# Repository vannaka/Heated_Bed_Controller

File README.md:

Heated_Bed_Controller

# PCB Images

# Prototyping

# Screen & Nob

# Wiring

# Bed & Printer

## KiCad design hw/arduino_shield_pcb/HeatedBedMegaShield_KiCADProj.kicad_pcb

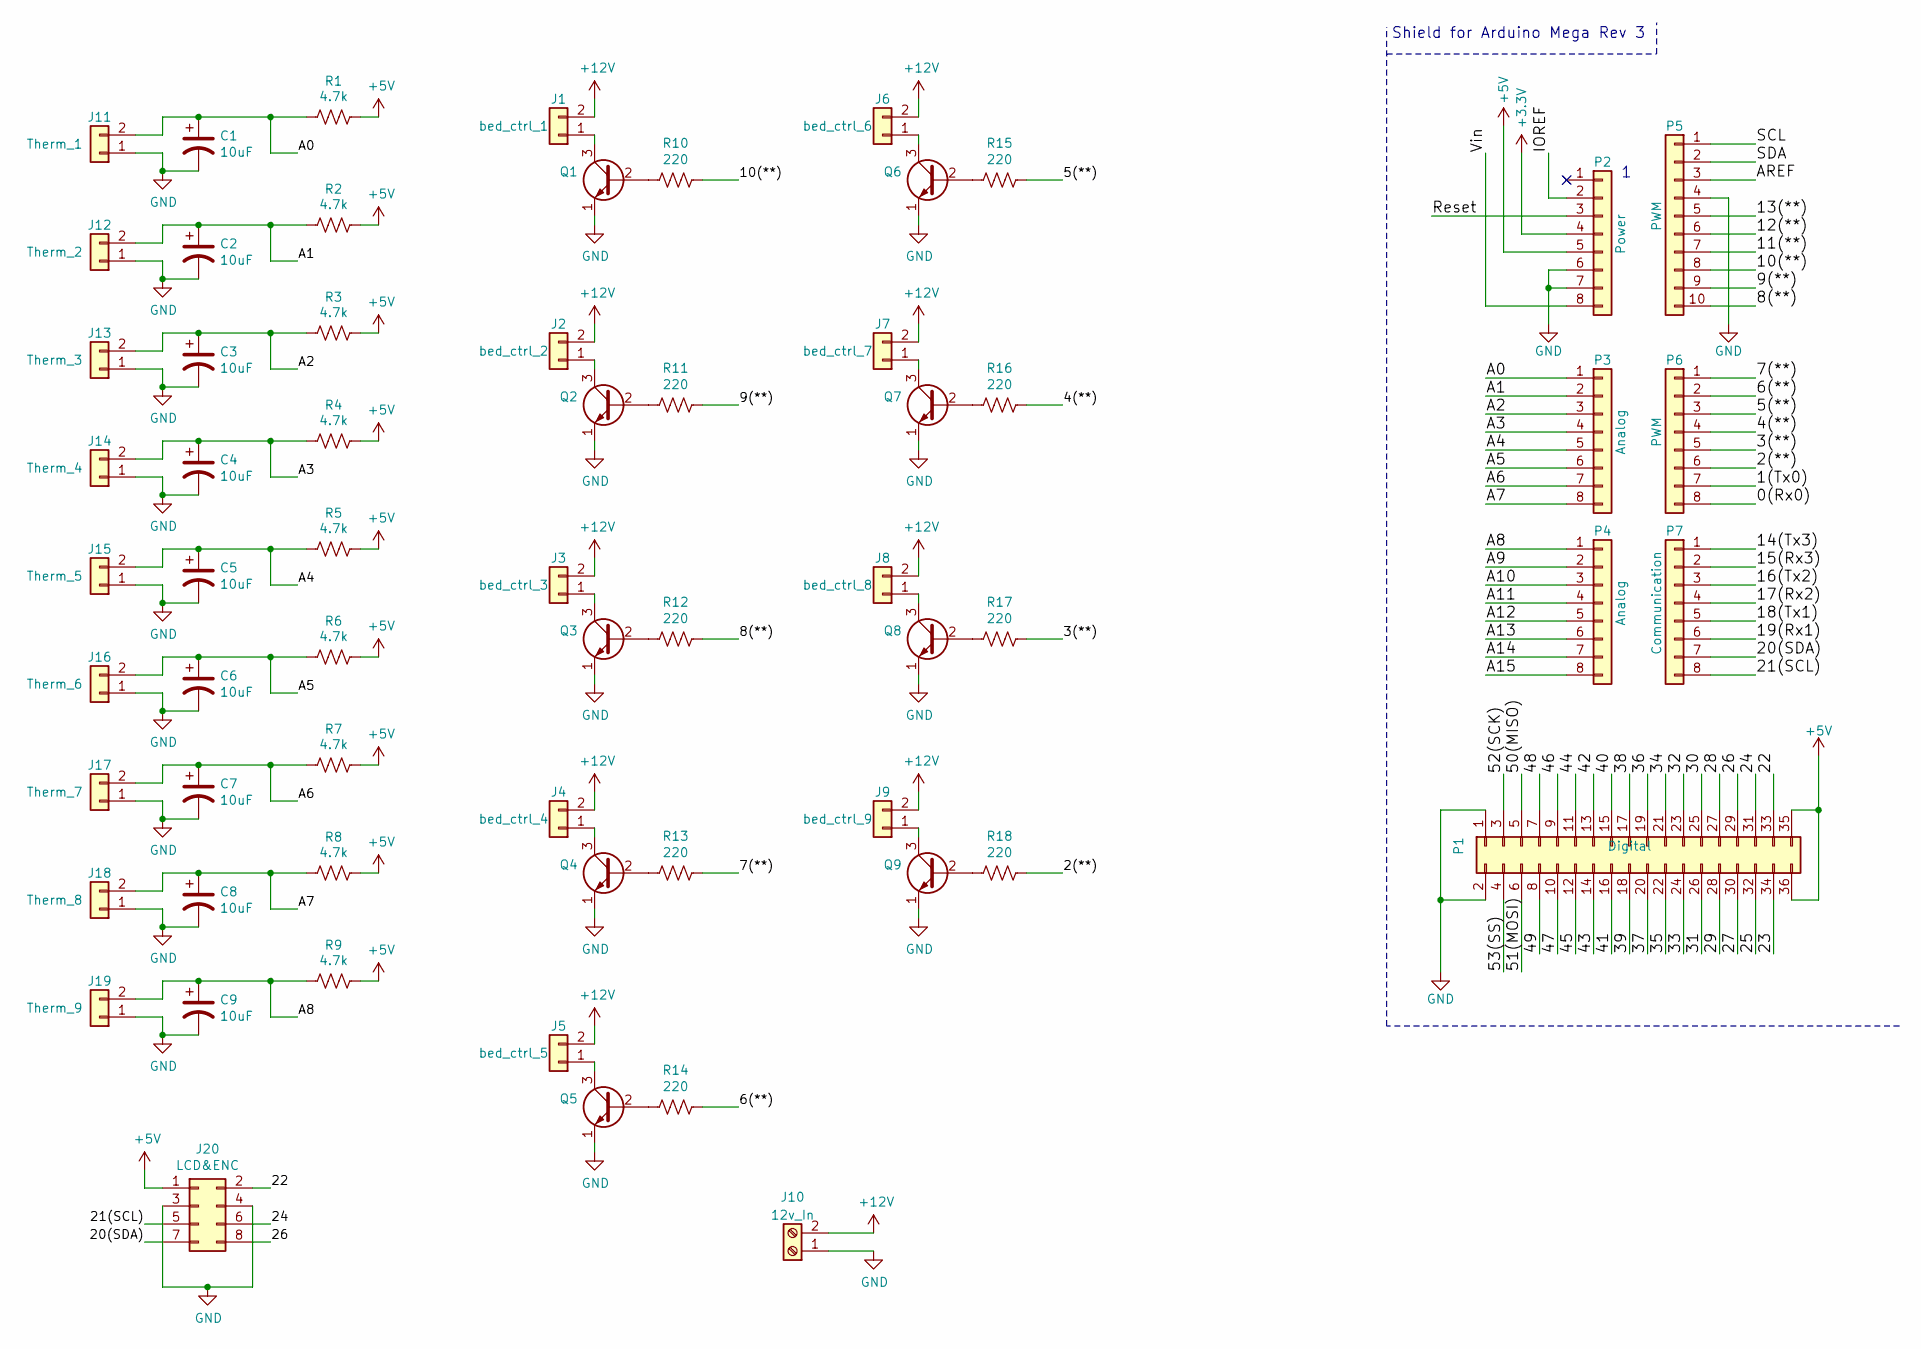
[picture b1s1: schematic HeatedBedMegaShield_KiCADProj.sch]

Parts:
C1, C2, C3, C4, C5, C6, C7, C8, C9: 10uF; CP_Radial_D4.0mm_P1.50mm
J1: bed_ctrl_1; PinHeader_1x02_P2.54mm_Vertical
J2: bed_ctrl_2; PinHeader_1x02_P2.54mm_Vertical
J3: bed_ctrl_3; PinHeader_1x02_P2.54mm_Vertical
J4: bed_ctrl_4; PinHeader_1x02_P2.54mm_Vertical
J5: bed_ctrl_5; PinHeader_1x02_P2.54mm_Vertical
J6: bed_ctrl_6; PinHeader_1x02_P2.54mm_Vertical
J7: bed_ctrl_7; PinHeader_1x02_P2.54mm_Vertical
J8: bed_ctrl_8; PinHeader_1x02_P2.54mm_Vertical
J9: bed_ctrl_9; PinHeader_1x02_P2.54mm_Vertical
J10: 12v_In; TerminalBlock_Phoenix_MKDS-1,5-2_1x02_P5.00mm_Horizontal
J11: Therm_1; PinHeader_1x02_P2.54mm_Vertical
J12: Therm_2; PinHeader_1x02_P2.54mm_Vertical
J13: Therm_3; PinHeader_1x02_P2.54mm_Vertical
J14: Therm_4; PinHeader_1x02_P2.54mm_Vertical
J15: Therm_5; PinHeader_1x02_P2.54mm_Vertical
J16: Therm_6; PinHeader_1x02_P2.54mm_Vertical
J17: Therm_7; PinHeader_1x02_P2.54mm_Vertical
J18: Therm_8; PinHeader_1x02_P2.54mm_Vertical
J19: Therm_9; PinHeader_1x02_P2.54mm_Vertical
J20: LCD&ENC; IDC-Header_2x04_P2.54mm_Vertical
P1: Digital; Socket_Strip_Arduino_2x18
P2: Power; Socket_Strip_Arduino_1x08
P3, P4: Analog; Socket_Strip_Arduino_1x08
P5: PWM; Socket_Strip_Arduino_1x10
P6: PWM; Socket_Strip_Arduino_1x08
P7: Communication; Socket_Strip_Arduino_1x08
Q1, Q2, Q3, Q4, Q5, Q6, Q7, Q8, Q9: Q_NPN_EBC; TO-92_Inline
R1, R2, R3, R4, R5, R6, R7, R8, R9: 4.7k; R_Axial_DIN0204_L3.6mm_D1.6mm_P5.08mm_Horizontal
R10, R11, R12, R13, R14, R15, R16, R17, R18: 220; R_Axial_DIN0204_L3.6mm_D1.6mm_P5.08mm_Horizontal

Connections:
+3V3: P2.4
+5V: J20.1, P1.35, P1.36, P2.5, R1.1, R2.1, R3.1, R4.1, R5.1, R6.1, R7.1, R8.1, R9.1
+12V: J1.2, J2.2, J3.2, J4.2, J5.2, J6.2, J7.2, J8.2, J9.2, J10.2
/0(Rx0): P6.8
/1(Tx0): P6.7
/2(**): P6.6, R18.1
/3(**): P6.5, R17.1
/4(**): P6.4, R16.1
/5(**): P6.3, R15.1
/6(**): P6.2, R14.1
/7(**): P6.1, R13.1
/8(**): P5.10, R12.1
/9(**): P5.9, R11.1
/10(**): P5.8, R10.1
/11(**): P5.7
/12(**): P5.6
/13(**): P5.5
/14(Tx3): P7.1
/15(Rx3): P7.2
/16(Tx2): P7.3
/17(Rx2): P7.4
/18(Tx1): P7.5
/19(Rx1): P7.6
/20(SDA): J20.7, P7.7
/21(SCL): J20.5, P7.8
/22: J20.2, P1.33
/23: P1.34
/24: J20.6, P1.31
/25: P1.32
/26: J20.8, P1.29
/27: P1.30
/28: P1.27
/29: P1.28
/30: P1.25
/31: P1.26
/32: P1.23
/33: P1.24
/34: P1.21
/35: P1.22
/36: P1.19
/37: P1.20
/38: P1.17
/39: P1.18
/40: P1.15
/41: P1.16
/42: P1.13
/43: P1.14
/44: P1.11
/45: P1.12
/46: P1.9
/47: P1.10
/48: P1.7
/49: P1.8
/50(MISO): P1.5
/51(MOSI): P1.6
/52(SCK): P1.3
/53(SS): P1.4
/A0: C1.1, J11.2, P3.1, R1.2
/A1: C2.1, J12.2, P3.2, R2.2
/A2: C3.1, J13.2, P3.3, R3.2
/A3: C4.1, J14.2, P3.4, R4.2
/A4: C5.1, J15.2, P3.5, R5.2
/A5: C6.1, J16.2, P3.6, R6.2
/A6: C7.1, J17.2, P3.7, R7.2
/A7: C8.1, J18.2, P3.8, R8.2
/A8: C9.1, J19.2, P4.1, R9.2
/A9: P4.2
/A10: P4.3
/A11: P4.4
/A12: P4.5
/A13: P4.6
/A14: P4.7
/A15: P4.8
/AREF: P5.3
/IOREF: P2.2
/Reset: P2.3
/SCL: P5.1
/SDA: P5.2
/Vin: P2.8
GND: C1.2, C2.2, C3.2, C4.2, C5.2, C6.2, C7.2, C8.2, C9.2, J10.1, J11.1, J12.1, J13.1, J14.1, J15.1, J16.1, J17.1, J18.1, J19.1, J20.3, J20.4, P1.1, P1.2, P2.6, P2.7, P5.4, Q1.1 (E), Q2.1 (E), Q3.1 (E), Q4.1 (E), Q5.1 (E), Q6.1 (E), Q7.1 (E), Q8.1 (E), Q9.1 (E)
unnamed: J1.1, Q1.3 (C)
unnamed: J2.1, Q2.3 (C)
unnamed: J3.1, Q3.3 (C)
unnamed: J4.1, Q4.3 (C)
unnamed: J5.1, Q5.3 (C)
unnamed: J6.1, Q6.3 (C)
unnamed: J7.1, Q7.3 (C)
unnamed: J8.1, Q8.3 (C)
unnamed: J9.1, Q9.3 (C)
unnamed: Q1.2 (B), R10.2
unnamed: Q2.2 (B), R11.2
unnamed: Q3.2 (B), R12.2
unnamed: Q4.2 (B), R13.2
unnamed: Q5.2 (B), R14.2
unnamed: Q6.2 (B), R15.2
unnamed: Q7.2 (B), R16.2
unnamed: Q8.2 (B), R17.2
unnamed: Q9.2 (B), R18.2

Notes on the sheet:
Shield for Arduino Mega Rev 3

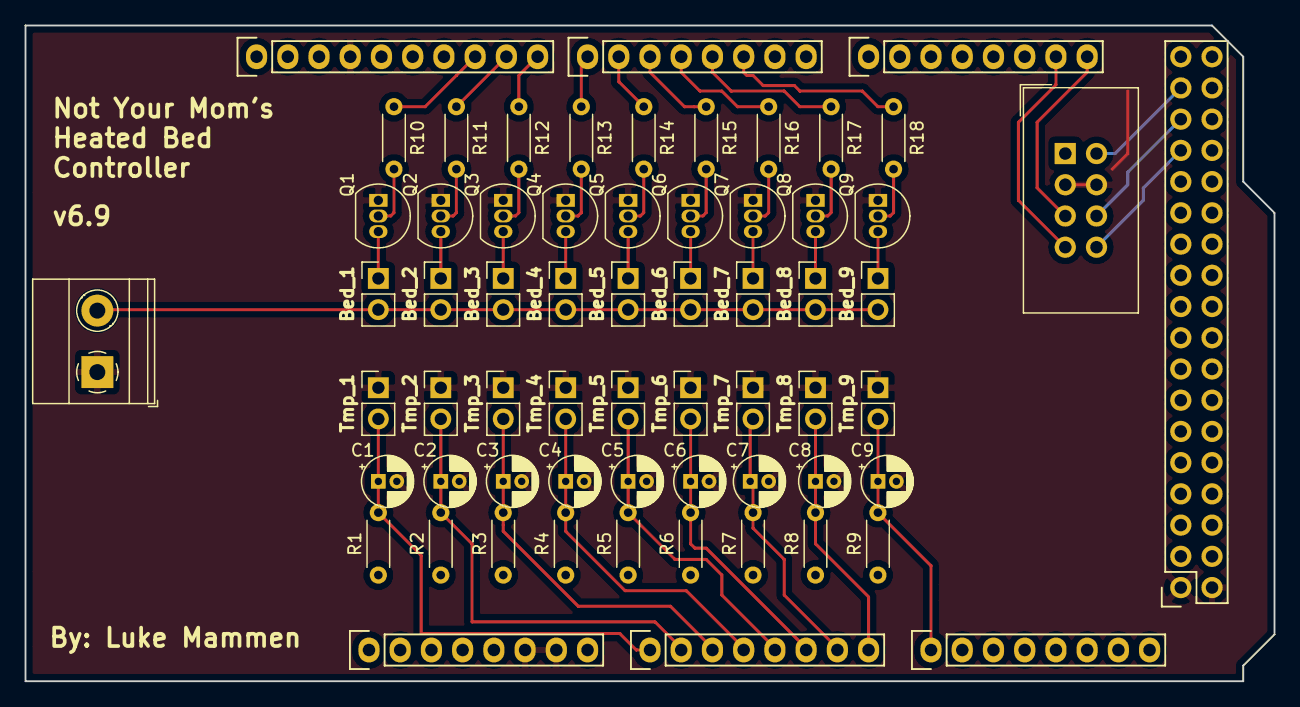
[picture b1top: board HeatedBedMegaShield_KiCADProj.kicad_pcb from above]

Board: 2 copper layers, 101.6 x 53.3 mm, 63 parts (0 on the bottom side), 44 nets.

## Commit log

2019-02-08 Added platformIO project.
2019-02-08 Started menu library
2019-02-11 Added menu structs
2019-02-11 small struct changes
2019-02-11 More menu work
2019-02-16 Switch to ArduinoMenu library for menu's.
2019-02-16 menu work
2019-02-24 Added info screen to show temps of all beds.
2019-03-02 Init local var to zero cause I'm a noob.
2019-03-04 Increase adc samples
2019-03-12 Start adding all 9 beds
2019-03-12 Get info screen displayed nicely.
2019-03-13 Use arrays for vars related to heated beds
2019-03-21 Add "all off" menu option in "All Beds" menu
2019-04-01 Comment formatting.
2019-04-06 The heaters now use software pwm to allow variable frequency.
2022-01-31 Fix compilation for newer versions of platformio.
2022-03-09 Add images to repo
2022-03-09 Add images to readme
2022-03-09 Add KiCAD files for arduino shield pcb.
